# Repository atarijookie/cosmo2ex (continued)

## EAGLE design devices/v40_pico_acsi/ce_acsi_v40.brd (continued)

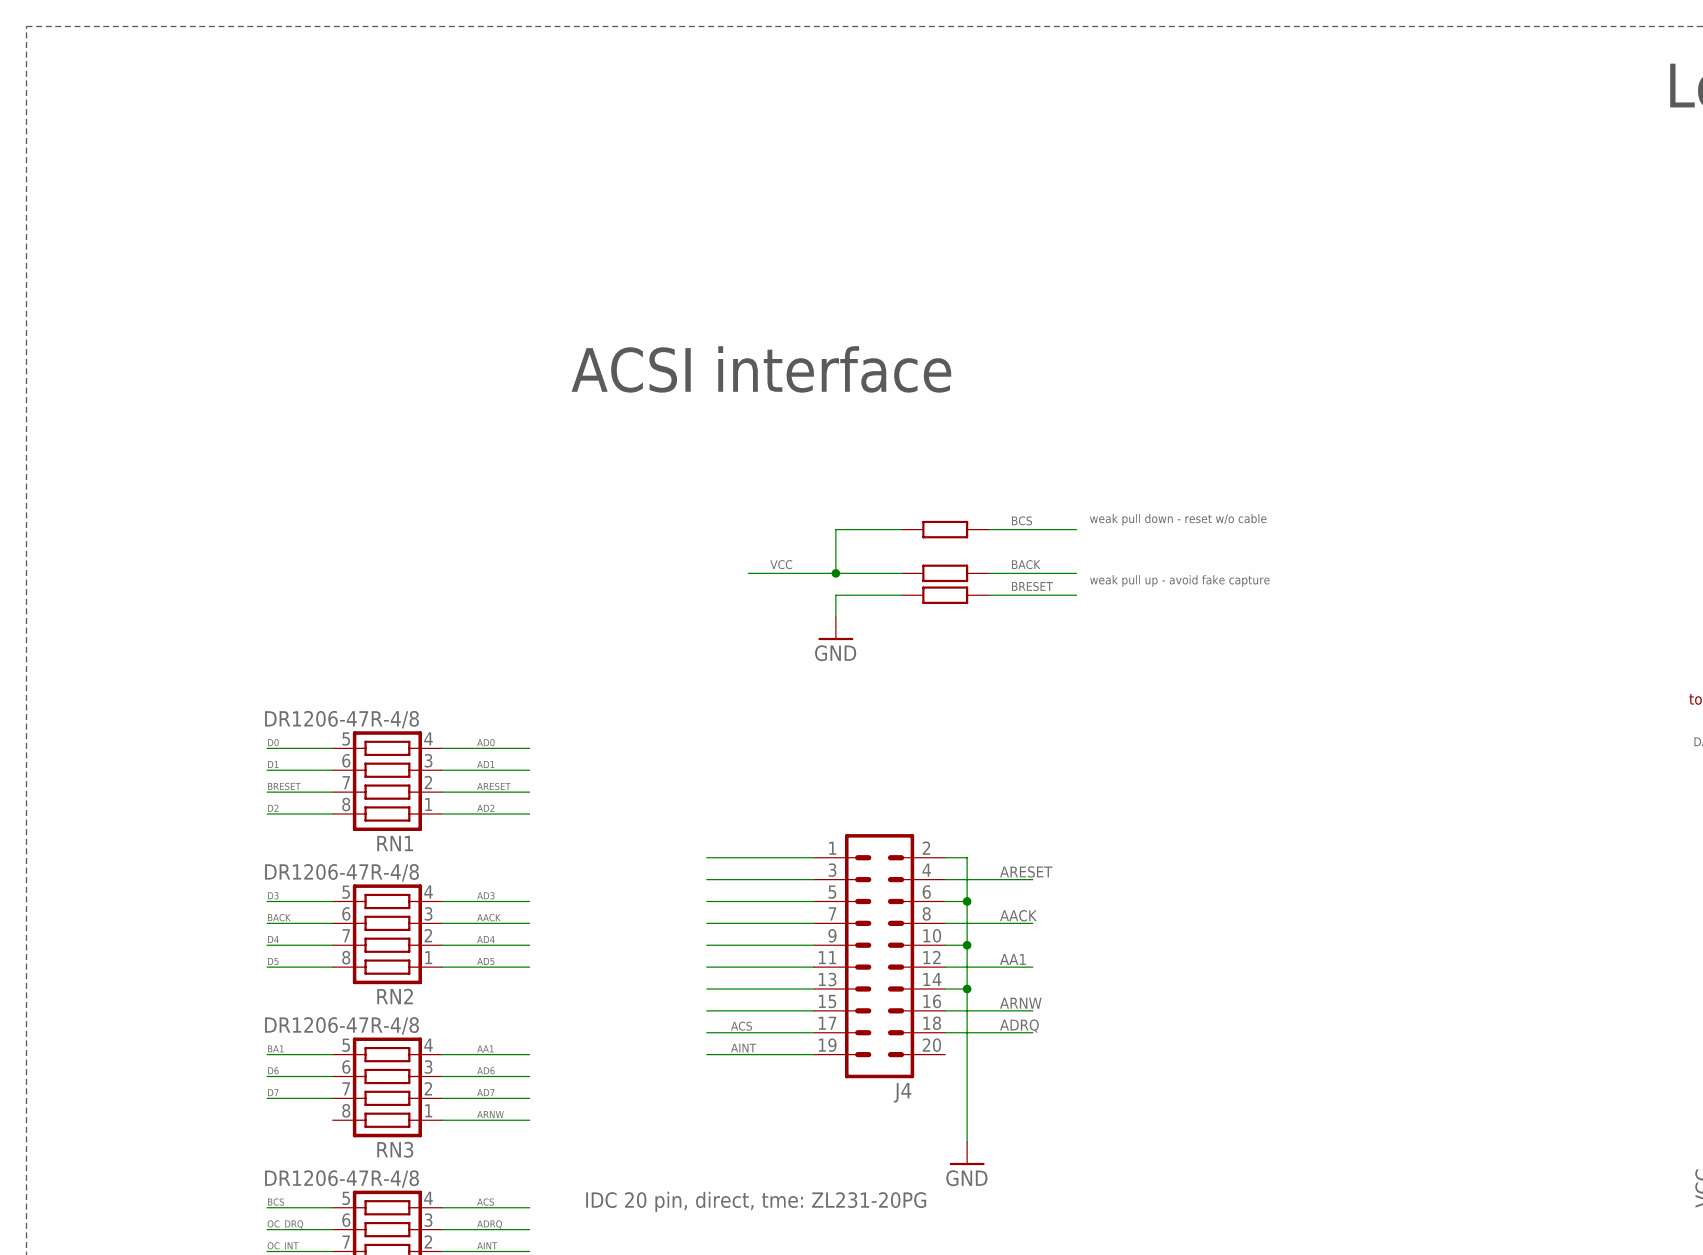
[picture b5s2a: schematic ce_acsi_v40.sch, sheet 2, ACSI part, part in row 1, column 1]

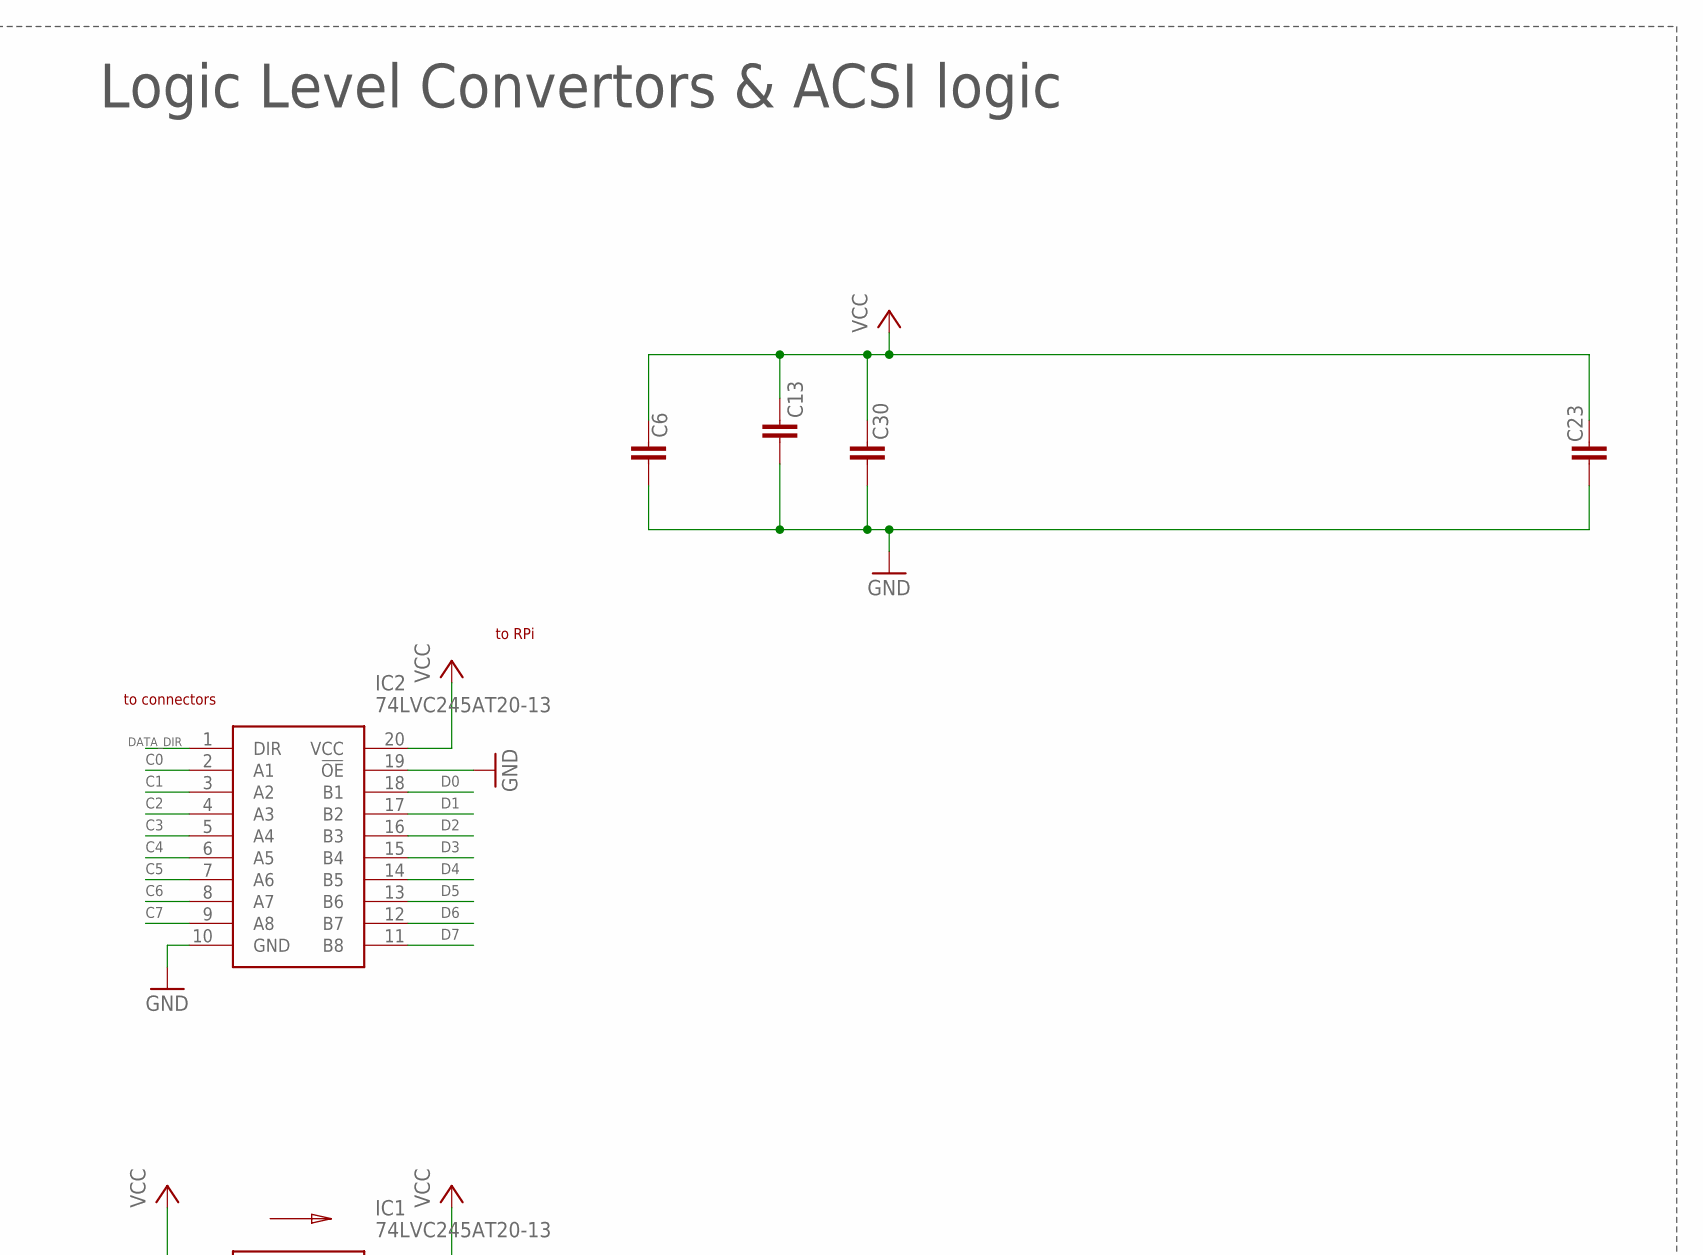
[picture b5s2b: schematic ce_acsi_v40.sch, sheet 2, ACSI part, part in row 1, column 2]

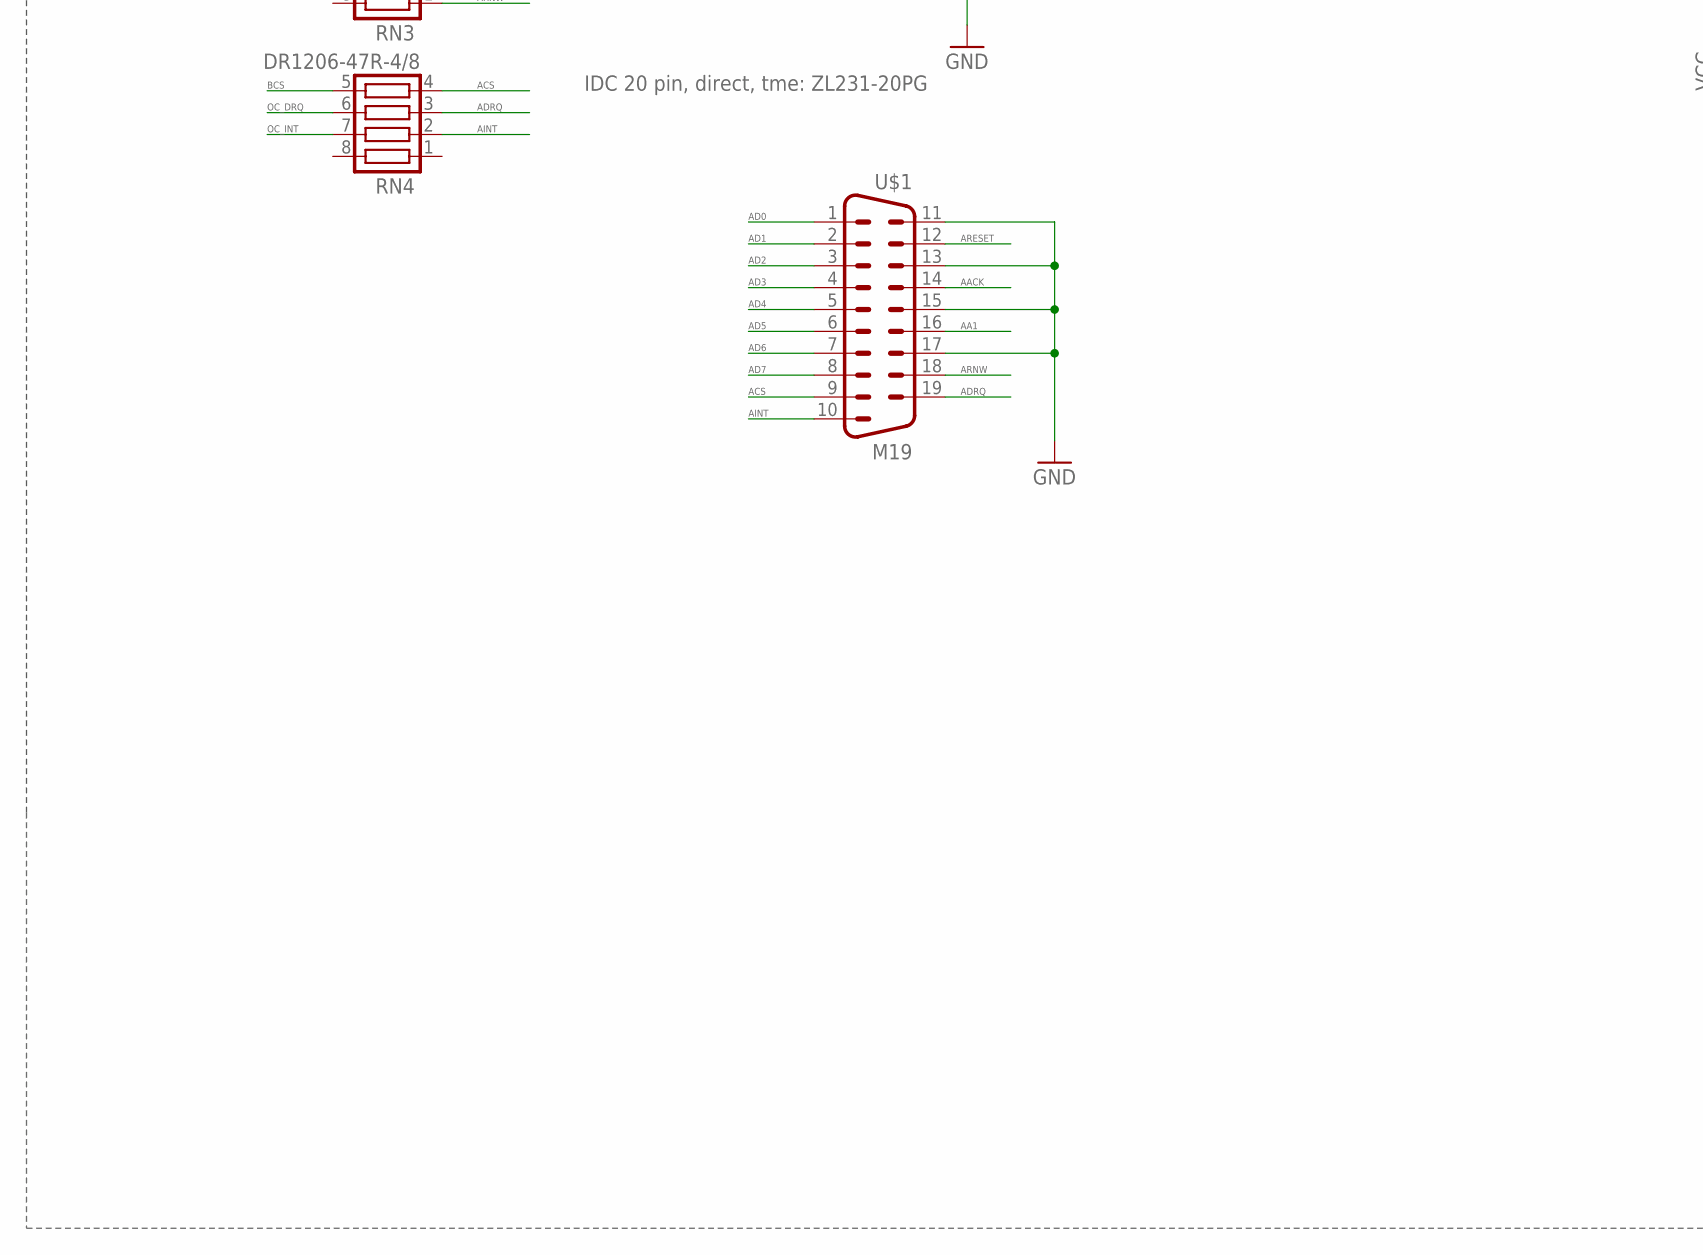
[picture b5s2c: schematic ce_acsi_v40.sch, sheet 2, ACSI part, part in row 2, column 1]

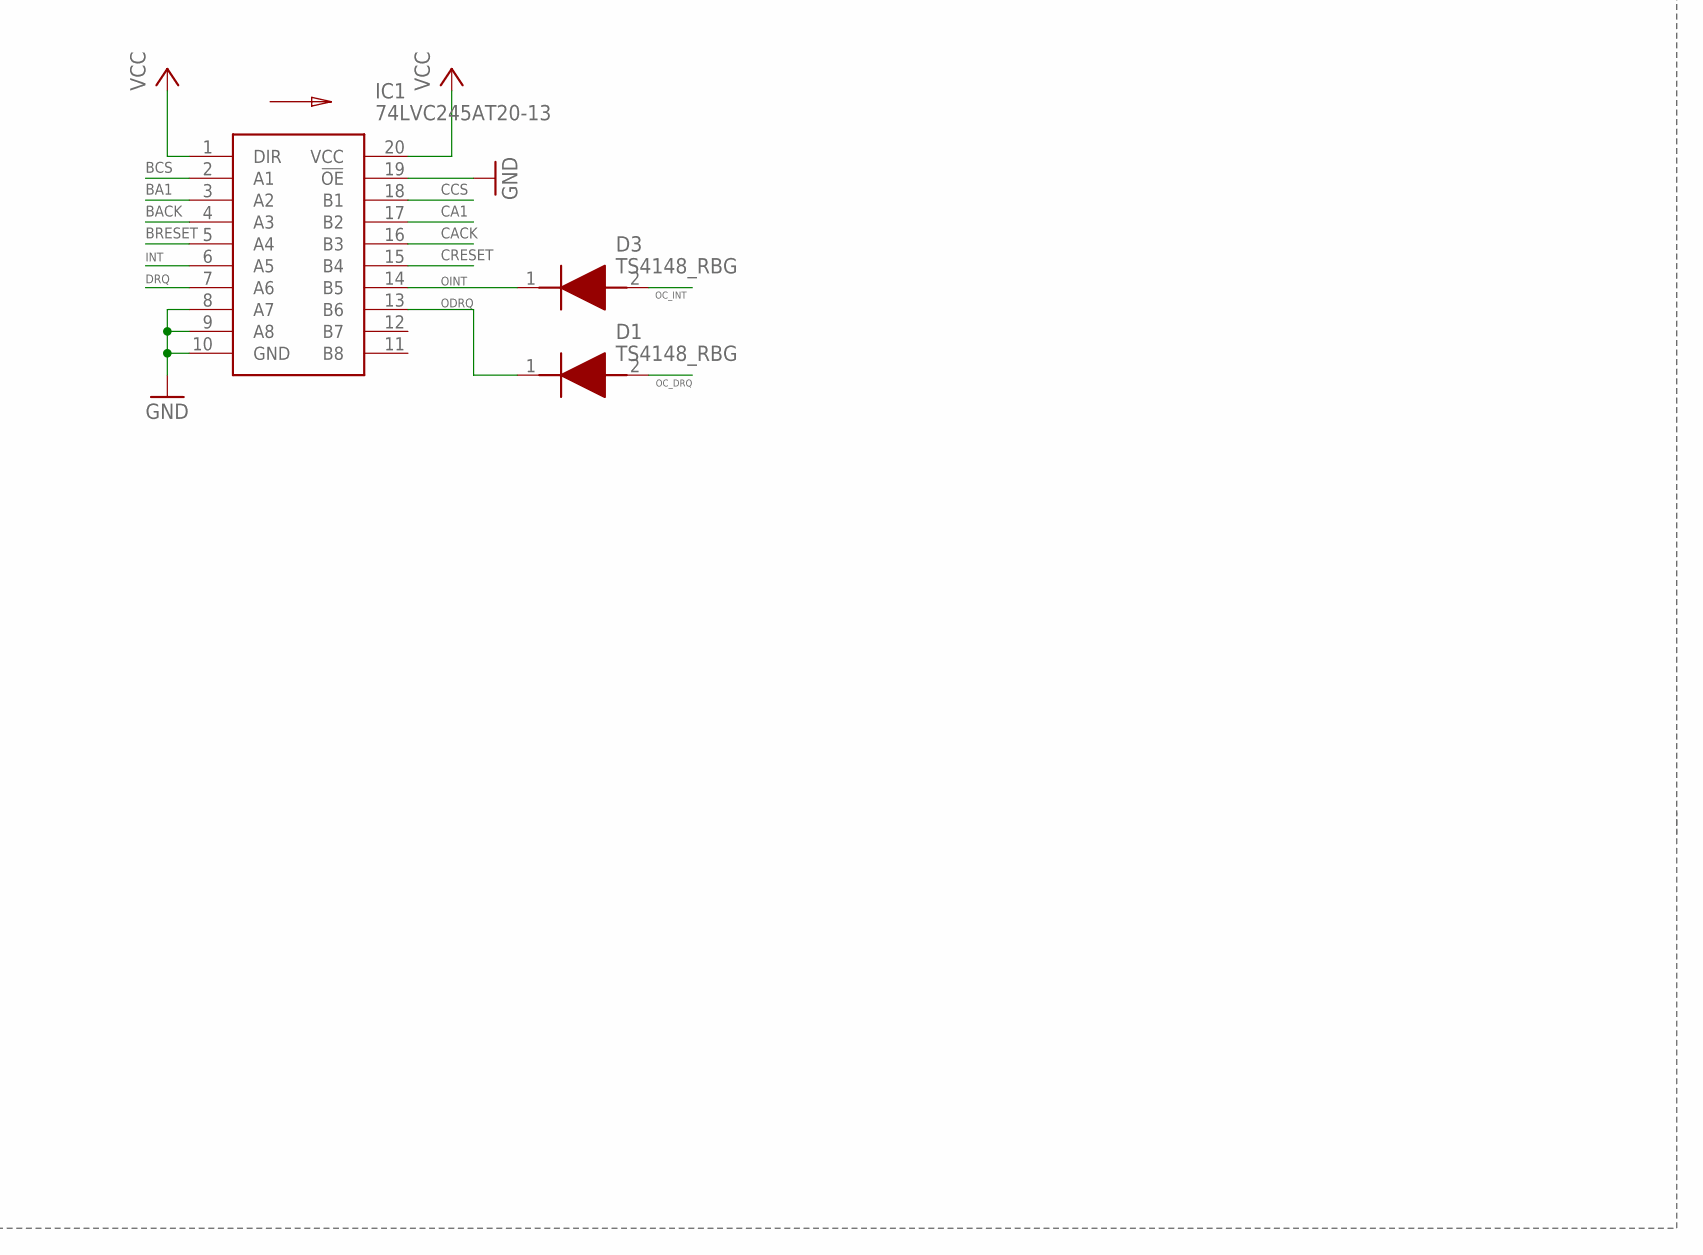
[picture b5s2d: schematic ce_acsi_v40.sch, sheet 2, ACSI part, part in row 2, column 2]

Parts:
C6, C13, C23: 100 nF; C0603
C30: 1 uF; C0805
D1: TS4148_RBG; DIOC2012X85N; MANUFACTURER_PART_NUMBER TS4148 RBG
D3: TS4148_RBG; DIOC2012X85N
IC1, IC2: 74LVC245AT20-13; SOP65P640X120-20N
J4: IDC 20 pin, direct, tme: ZL231-20PG; ML20
R30, R31, R32: 10k; R0603
RN1, RN2, RN3, RN4: DR1206-47R-4/8; CTS742C083
U$1: M19

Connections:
AA1: J4.12, RN3.4, U$1.16
AACK: J4.8, RN2.3, U$1.14
ACS: J4.17, RN4.4, U$1.9
AD0: J4.1, RN1.4, U$1.1
AD1: J4.3, RN1.3, U$1.2
AD2: J4.5, RN1.1, U$1.3
AD3: J4.7, RN2.4, U$1.4
AD4: J4.9, RN2.2, U$1.5
AD5: J4.11, RN2.1, U$1.6
AD6: J4.13, RN3.3, U$1.7
AD7: J4.15, RN3.2, U$1.8
ADRQ: J4.18, RN4.3, U$1.19
AINT: J4.19, RN4.2, U$1.10
ARESET: J4.4, RN1.2, U$1.12
ARNW: J4.16, RN3.1, U$1.18
BA1: IC1.3 (A2), RN3.5
BACK: IC1.4 (A3), R31.2, RN2.6
BCS: IC1.2 (A1), R32.2, RN4.5
BRESET: IC1.5 (A4), R30.2, RN1.7
C0: IC2.2 (A1); also elsewhere on the board
C1: IC2.3 (A2); also elsewhere on the board
C2: IC2.4 (A3); also elsewhere on the board
C3: IC2.5 (A4); also elsewhere on the board
C4: IC2.6 (A5); also elsewhere on the board
C5: IC2.7 (A6); also elsewhere on the board
C6: IC2.8 (A7); also elsewhere on the board
C7: IC2.9 (A8); also elsewhere on the board
CA1: IC1.17 (B2); also elsewhere on the board
CACK: IC1.16 (B3); also elsewhere on the board
CCS: IC1.18 (B1); also elsewhere on the board
CRESET: IC1.15 (B4); also elsewhere on the board
D0: IC2.18 (B1), RN1.5
D1: IC2.17 (B2), RN1.6
D2: IC2.16 (B3), RN1.8
D3: IC2.15 (B4), RN2.5
D4: IC2.14 (B5), RN2.7
D5: IC2.13 (B6), RN2.8
D6: IC2.12 (B7), RN3.6
D7: IC2.11 (B8), RN3.7
DATA_DIR: IC2.1 (DIR); also elsewhere on the board
DRQ: IC1.7 (A6); also elsewhere on the board
GND: C6.2, C13.2, C23.2, C30.2, IC1.8 (A7), IC1.9 (A8), IC1.10 (GND), IC1.19 (!OE), IC2.10 (GND), IC2.19 (!OE), J4.2, J4.6, J4.10, J4.14, R30.1, U$1.11, U$1.13, U$1.15, U$1.17; also elsewhere on the board
INT: IC1.6 (A5); also elsewhere on the board
OC_DRQ: D1.2 (A), RN4.6
OC_INT: D3.2 (A), RN4.7
ODRQ: D1.1 (K), IC1.13 (B6)
OINT: D3.1 (K), IC1.14 (B5)
VCC: C6.1, C13.1, C23.1, C30.1, IC1.1 (DIR), IC1.20 (VCC), IC2.20 (VCC), R31.1, R32.1; also elsewhere on the board

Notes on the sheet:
ACSI interface
to connectors
to RPi
Logic Level Convertors & ACSI logic
weak pull down - reset w/o cable
weak pull up - avoid fake capture

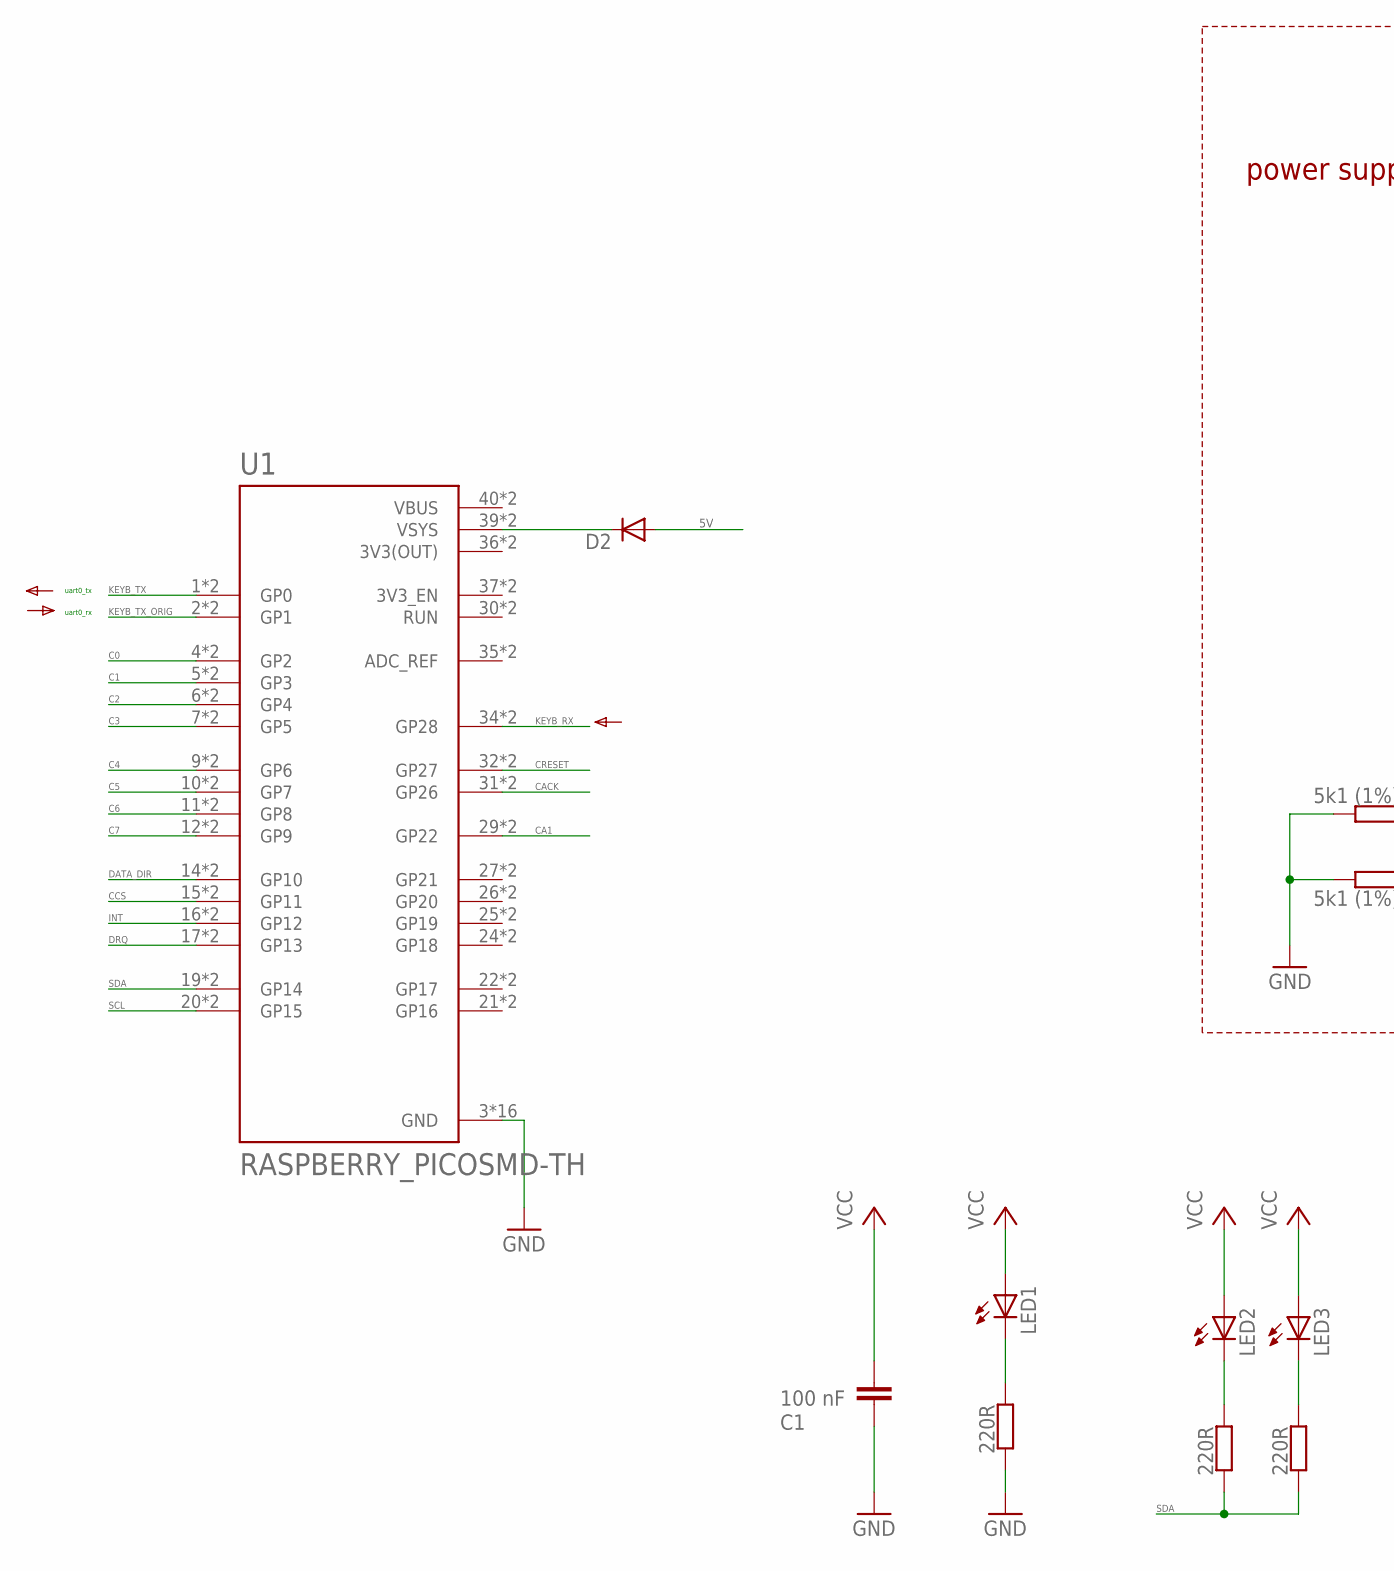
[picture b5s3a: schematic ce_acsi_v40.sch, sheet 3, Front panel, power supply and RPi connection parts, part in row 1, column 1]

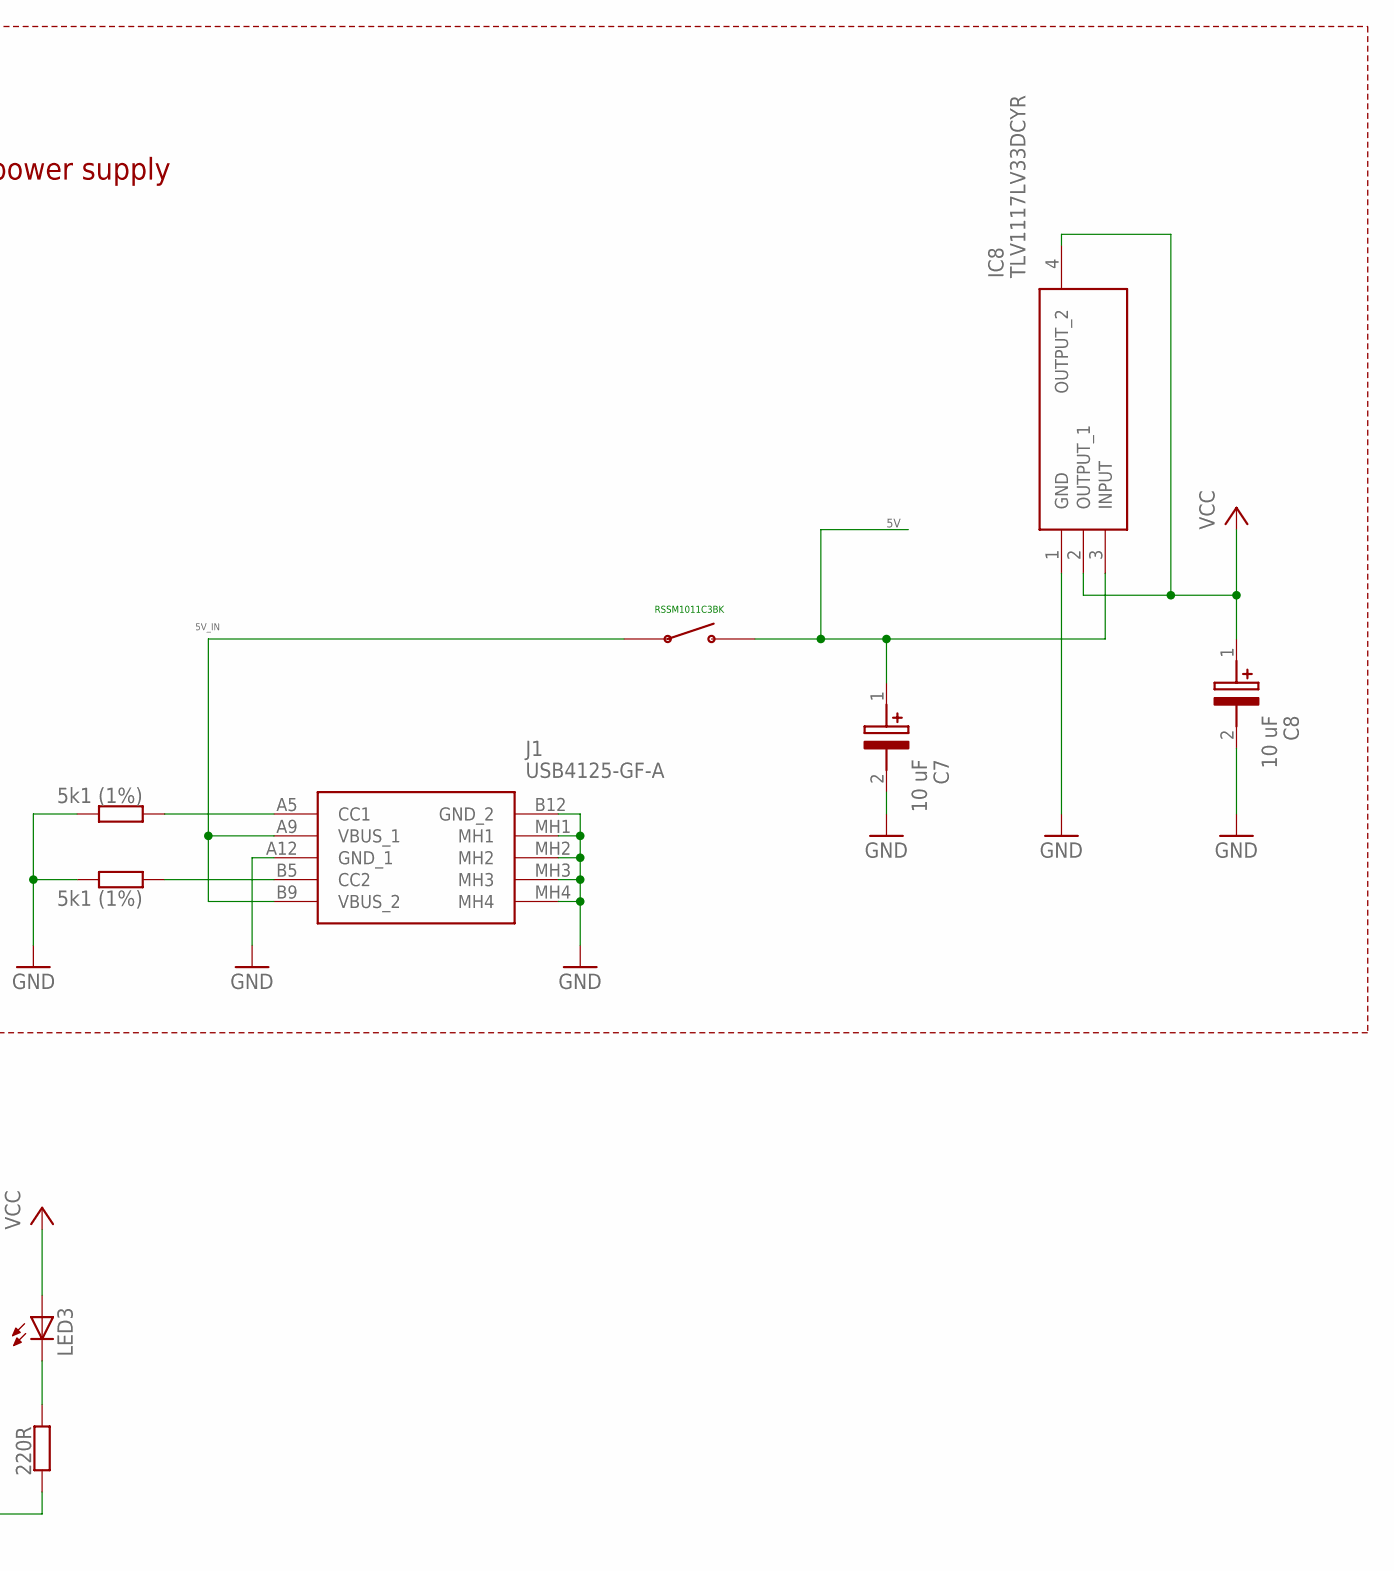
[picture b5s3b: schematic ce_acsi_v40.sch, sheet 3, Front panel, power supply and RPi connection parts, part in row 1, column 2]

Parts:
C1: 100 nF; C0603
C7, C8: 10 uF; CAPPM3528X210N
D2: SK110-DIO; DO214AC
IC8: TLV1117LV33DCYR; SOT230P700X180-4N
J1: USB4125-GF-A; USB4125GFA
LED1, LED2, LED3: LEDSML0603; SML0603
R2, R3, R18: 220R; R0603
R14, R17: 5k1 (1%); R0603
U1: RASPBERRY_PICOSMD-TH; PICO-PKG
U$2: RSSM1011C3BK

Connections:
3V3(OUT): U1.36 (3V3(OUT)), U1.P$36 (3V3(OUT))
5V: C7.1 (+), D2.A, IC8.3 (INPUT), U$2.P$2; also elsewhere on the board
5V_IN: J1.A9 (VBUS_1), J1.B9 (VBUS_2), U$2.P$1
C0: U1.4 (GP2), U1.P$4 (GP2); also elsewhere on the board
C1: U1.5 (GP3), U1.P$5 (GP3); also elsewhere on the board
C2: U1.6 (GP4), U1.P$6 (GP4); also elsewhere on the board
C3: U1.7 (GP5), U1.P$7 (GP5); also elsewhere on the board
C4: U1.9 (GP6), U1.P$9 (GP6); also elsewhere on the board
C5: U1.10 (GP7), U1.P$10 (GP7); also elsewhere on the board
C6: U1.11 (GP8), U1.P$11 (GP8); also elsewhere on the board
C7: U1.12 (GP9), U1.P$12 (GP9); also elsewhere on the board
CA1: U1.29 (GP22), U1.P$29 (GP22); also elsewhere on the board
CACK: U1.31 (GP26), U1.P$31 (GP26); also elsewhere on the board
CCS: U1.15 (GP11), U1.P$15 (GP11); also elsewhere on the board
CRESET: U1.32 (GP27), U1.P$32 (GP27); also elsewhere on the board
DATA_DIR: U1.14 (GP10), U1.P$14 (GP10); also elsewhere on the board
DRQ: U1.17 (GP13), U1.P$17 (GP13); also elsewhere on the board
GND: C1.2, C7.2 (-), C8.2 (-), IC8.1 (GND), J1.A12 (GND_1), J1.B12 (GND_2), J1.MH1, J1.MH2, J1.MH3, J1.MH4, R14.2, R17.2, R18.2, U1.3 (GND), U1.8 (GND), U1.13 (GND), U1.18 (GND), U1.23 (GND), U1.28 (GND), U1.33 (GND), U1.38 (GND), U1.P$3 (GND), U1.P$8 (GND), U1.P$13 (GND), U1.P$18 (GND), U1.P$23 (GND), U1.P$28 (GND), U1.P$33 (GND), U1.P$38 (GND); also elsewhere on the board
INT: U1.16 (GP12), U1.P$16 (GP12); also elsewhere on the board
KEYB_RX: U1.34 (GP28), U1.P$34 (GP28); also elsewhere on the board
KEYB_TX: U1.1 (GP0), U1.P$1 (GP0); also elsewhere on the board
KEYB_TX_ORIG: U1.2 (GP1), U1.P$2 (GP1); also elsewhere on the board
unnamed: J1.B5 (CC2), R14.1
unnamed: J1.A5 (CC1), R17.1
unnamed: LED2.C, R2.1
unnamed: LED3.C, R3.1
unnamed: LED1.C, R18.1
unnamed: D2.C, U1.39 (VSYS), U1.P$39 (VSYS)
SCL: U1.20 (GP15), U1.P$20 (GP15)
SDA: R2.2, R3.2, U1.19 (GP14), U1.P$19 (GP14)
VBUS: U1.40 (VBUS), U1.P$40 (VBUS)
VCC: C1.1, C8.1 (+), IC8.2 (OUTPUT_1), IC8.4 (OUTPUT_2), LED1.A, LED2.A, LED3.A; also elsewhere on the board

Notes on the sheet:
power supply
uart0_rx
uart0_tx
RSSM1011C3BK

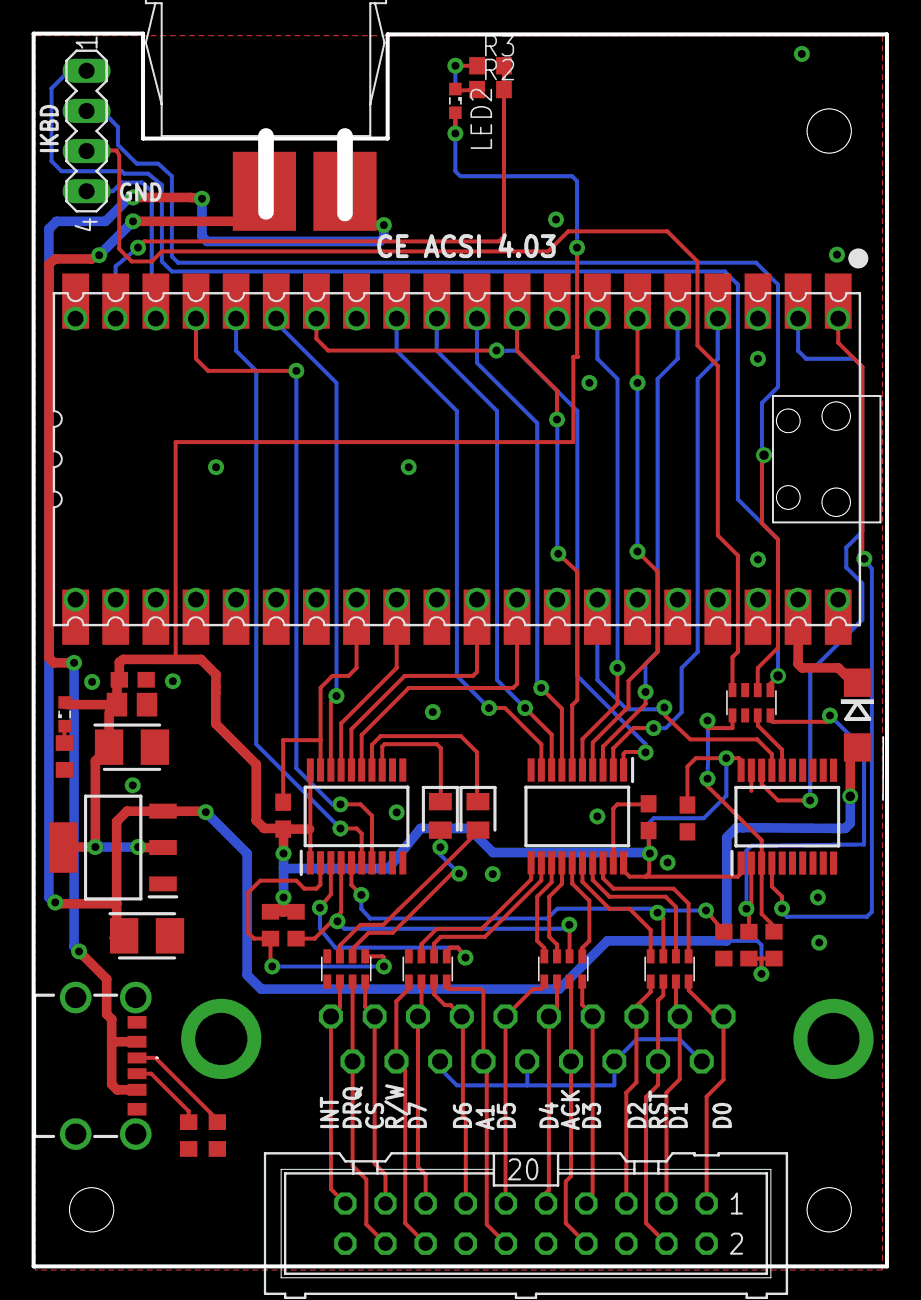
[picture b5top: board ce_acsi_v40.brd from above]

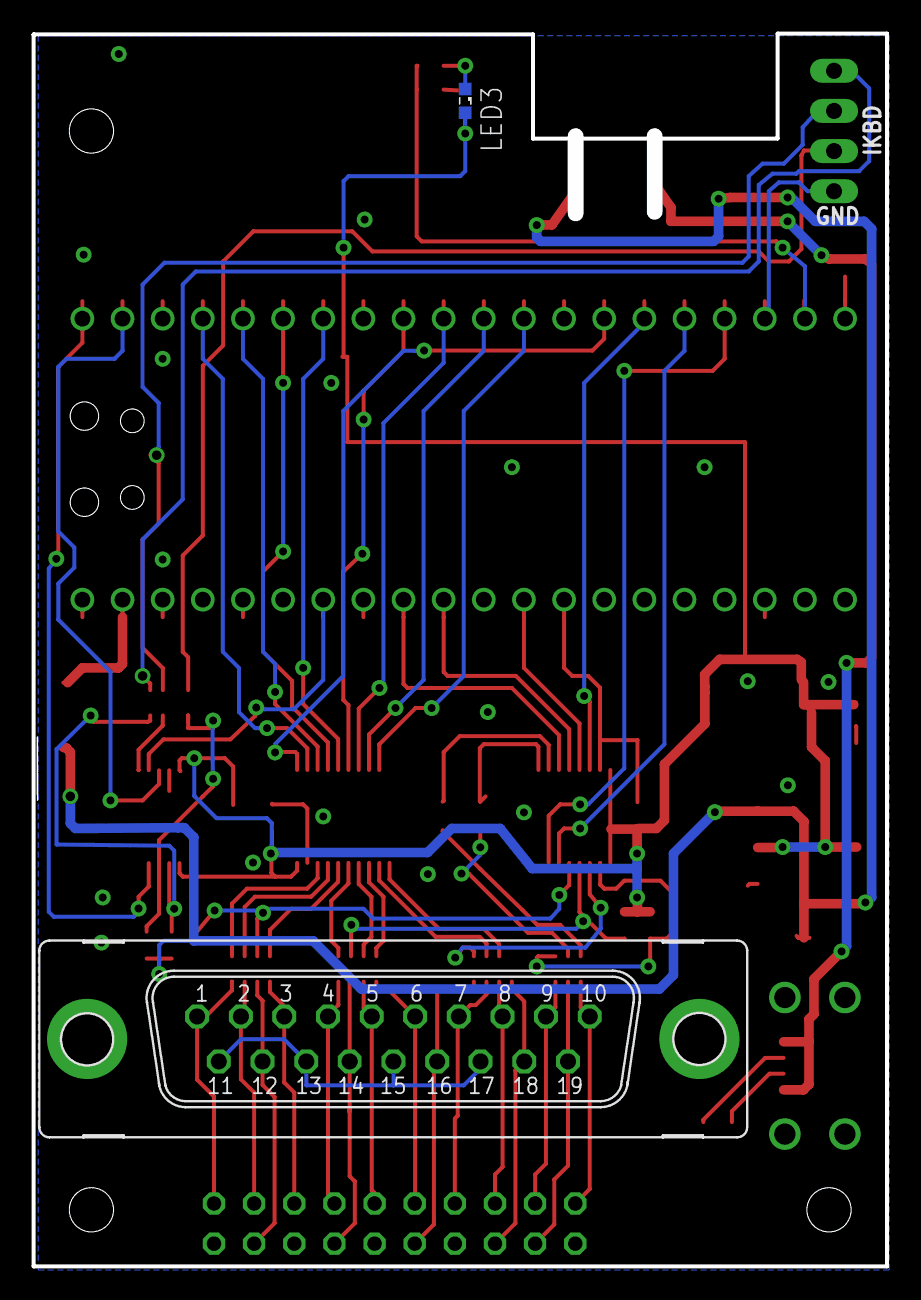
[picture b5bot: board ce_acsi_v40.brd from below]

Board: 2 copper layers, 54.0 x 78.0 mm, 38 parts (2 on the bottom side), 69 nets.

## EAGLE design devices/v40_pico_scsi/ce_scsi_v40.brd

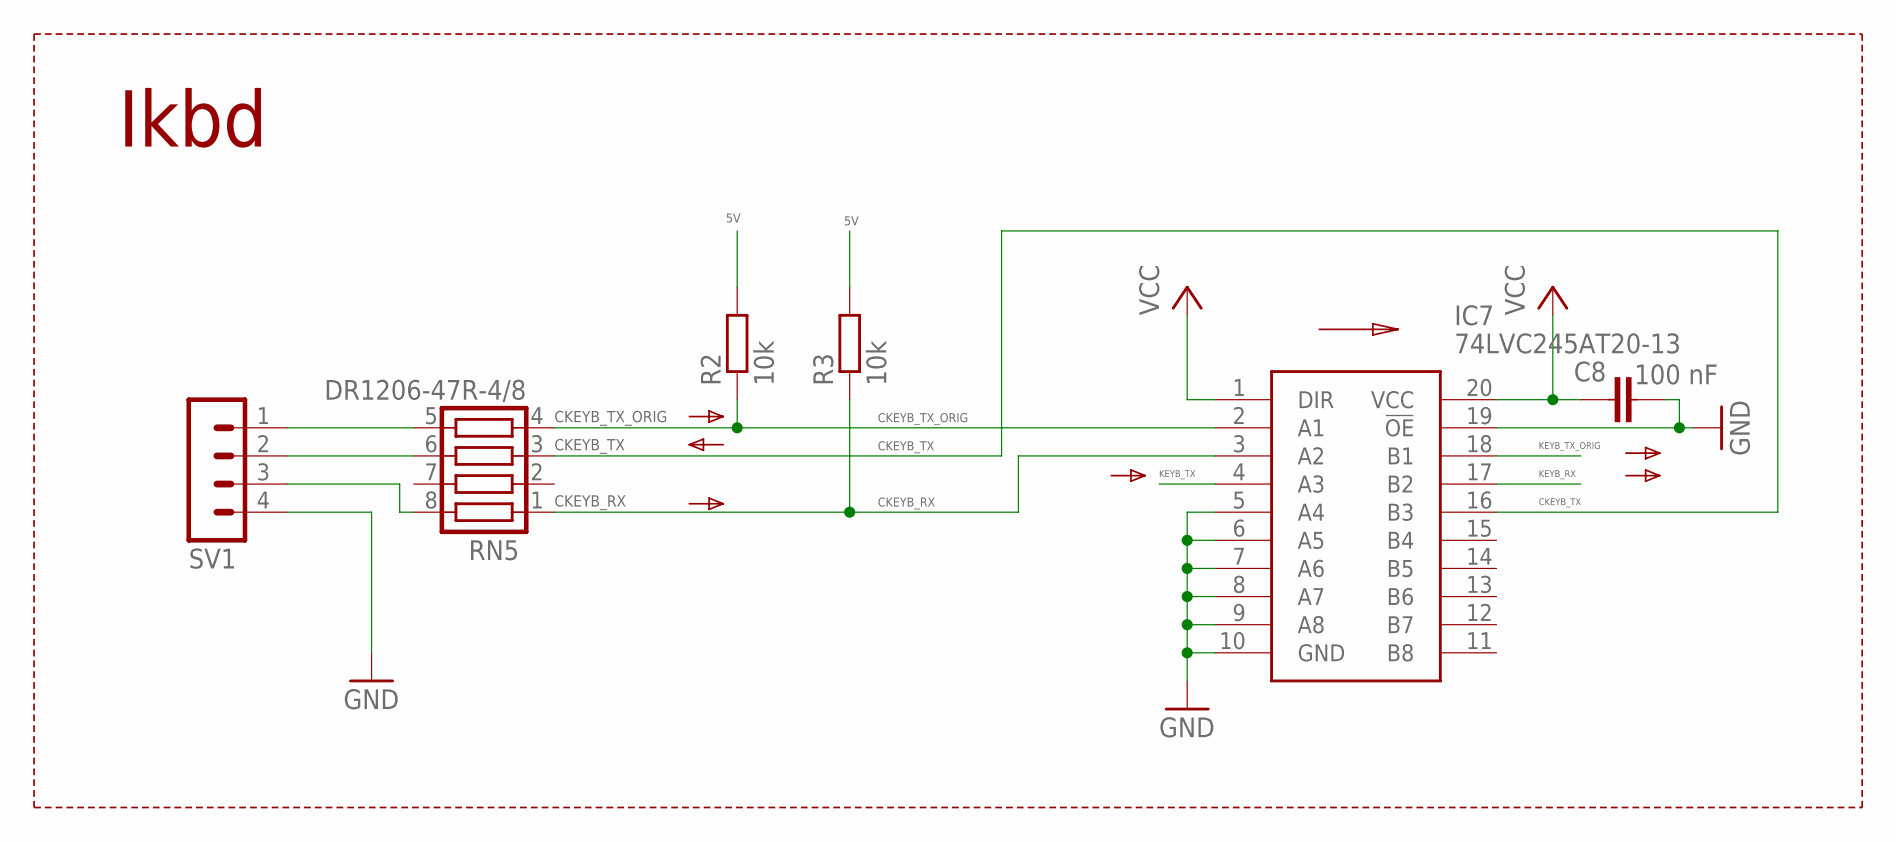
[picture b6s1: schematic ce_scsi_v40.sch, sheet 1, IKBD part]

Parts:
C8: 100 nF; C0603
IC7: 74LVC245AT20-13; SOP65P640X120-20N
R2, R3: 10k; R0603
RN5: DR1206-47R-4/8; CTS742C083
SV1: MA04-1

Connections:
5V: R2.2, R3.2; also elsewhere on the board
CKEYB_RX: IC7.3 (A2), R3.1, RN5.1
CKEYB_TX: IC7.16 (B3), RN5.3
CKEYB_TX_ORIG: IC7.2 (A1), R2.1, RN5.4
GND: C8.1, IC7.5 (A4), IC7.6 (A5), IC7.7 (A6), IC7.8 (A7), IC7.9 (A8), IC7.10 (GND), IC7.19 (!OE), SV1.4; also elsewhere on the board
KEYB_RX: IC7.17 (B2); also elsewhere on the board
KEYB_TX: IC7.4 (A3); also elsewhere on the board
KEYB_TX_ORIG: IC7.18 (B1); also elsewhere on the board
unnamed: RN5.6, SV1.2
VCC: C8.2, IC7.1 (DIR), IC7.20 (VCC); also elsewhere on the board
ZKEYB_RX: RN5.8, SV1.3
ZKEYB_TX_ORIG: RN5.5, SV1.1

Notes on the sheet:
Ikbd
